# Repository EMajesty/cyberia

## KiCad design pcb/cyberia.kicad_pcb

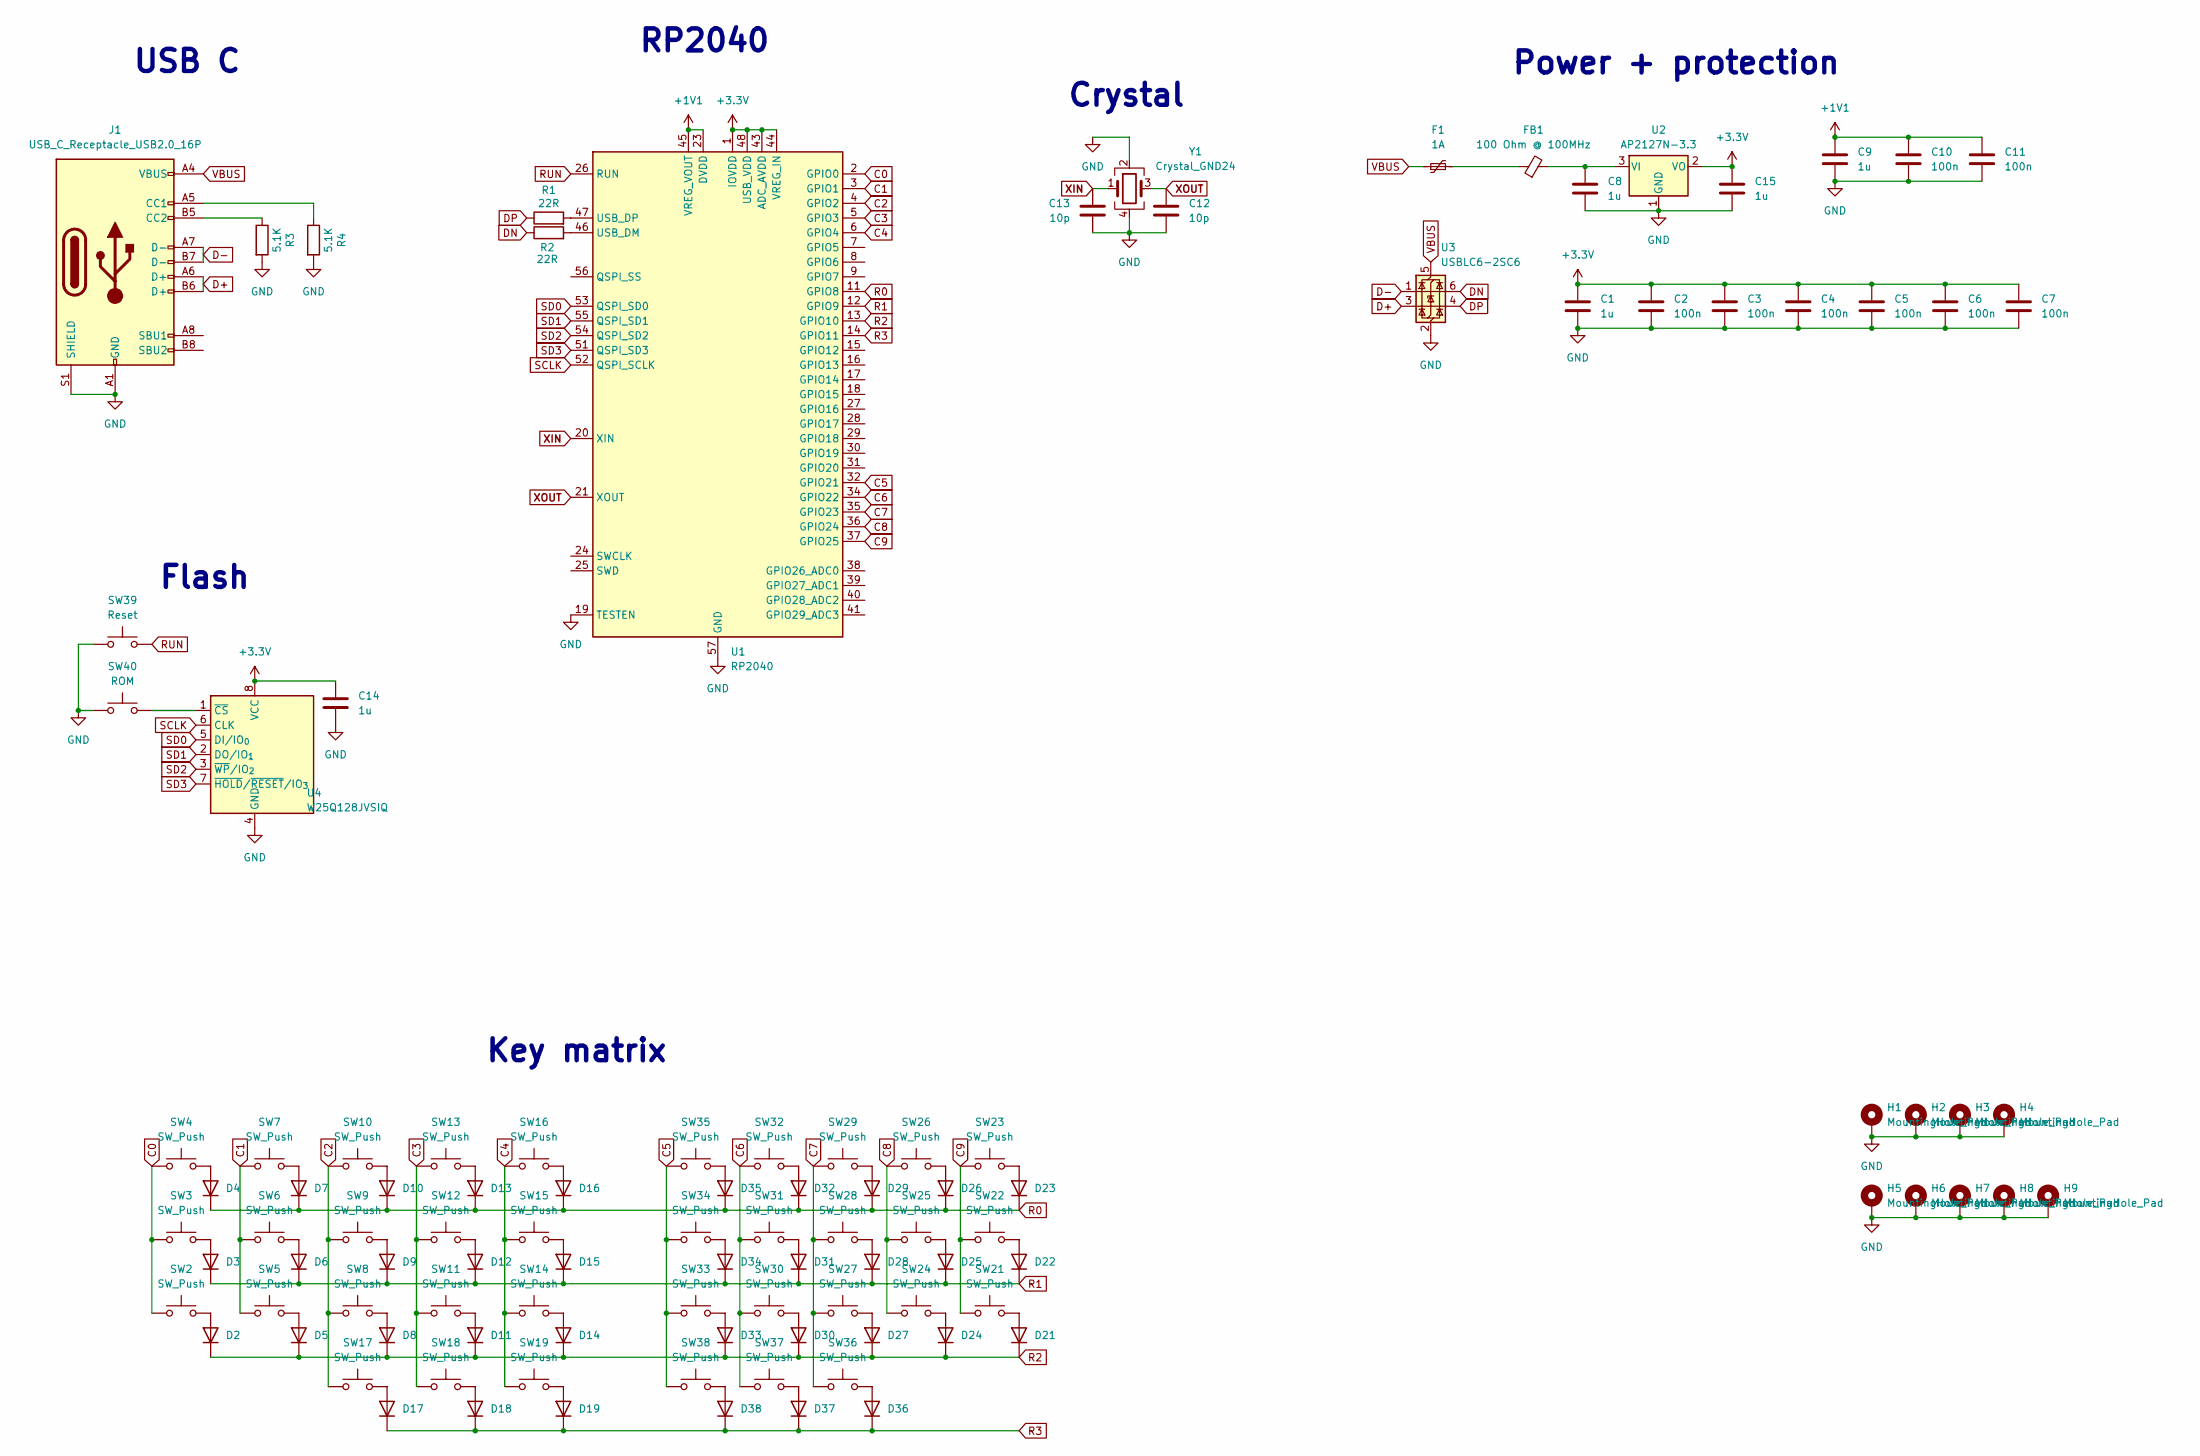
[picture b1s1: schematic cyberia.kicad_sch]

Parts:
C1, C8, C9, C14, C15: 1u; C_0603_1608Metric; LCSC C1592
C2, C3, C4, C5, C6, C7, C10, C11: 100n; C_0603_1608Metric; LCSC C1590
C12, C13: 10p; C_0603_1608Metric; LCSC C1634
D2, D3, D4, D5, D6, D7, D8, D9, D10, D11, D12, D13, D14, D15, D16, D17, D18, D19, D21, D22, D23, D24, D25, D26, D27, D28, D29, D30, D31, D32, D33, D34, D35, D36, D37, D38: D_Small_Filled; D_MiniMELF; LCSC C68883
F1: 1A; Fuse_0805_2012Metric; LCSC C20980
FB1: 100 Ohm @ 100MHz; R_0805_2012Metric; LCSC C1015
H1, H2, H3, H4, H5, H6, H7, H8, H9: MountingHole_Pad; MountingHole_3.2mm_M3
J1: USB_C_Receptacle_USB2.0_16P; USB_C_Receptacle_GCT_USB4105-xx-A_16P_TopMnt_Horizontal; LCSC C2894897
R1, R2: 22R; R_0603_1608Metric; LCSC C23345
R3, R4: 5.1K; R_0603_1608Metric; LCSC C23186
SW2, SW3, SW4, SW5, SW6, SW7, SW8, SW9, SW10, SW11, SW12, SW13, SW14, SW15, SW16, SW17, SW18, SW19, SW21, SW22, SW23, SW24, SW25, SW26, SW27, SW28, SW29, SW30, SW31, SW32, SW33, SW34, SW35, SW36, SW37, SW38: SW_Push
SW39: Reset; SW_SPST_TL3342
SW40: ROM; SW_SPST_TL3342
U1: RP2040; QFN-56-1EP_7x7mm_P0.4mm_EP3.2x3.2mm; LCSC C2040
U2: AP2127N-3.3; SOT-23; LCSC C176954
U3: USBLC6-2SC6; SOT-23-6; LCSC C7519
U4: W25Q128JVSIQ; SOIC-8_5.3x5.3mm_P1.27mm; LCSC C97521
Y1: Crystal_GND24; Crystal_SMD_3225-4Pin_3.2x2.5mm; LCSC C20625731

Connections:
+1V1: C9.1, C10.1, C11.1, U1.23 (DVDD), U1.45 (VREG_VOUT), U1.50 (DVDD)
+3.3V: C1.1, C2.1, C3.1, C4.1, C5.1, C6.1, C7.1, C14.1, C15.1, U1.1 (IOVDD), U1.10 (IOVDD), U1.22 (IOVDD), U1.33 (IOVDD), U1.42 (IOVDD), U1.43 (ADC_AVDD), U1.44 (VREG_IN), U1.48 (USB_VDD), U1.49 (IOVDD), U2.2 (VO), U4.8 (VCC)
C0: SW2.1, SW3.1, SW4.1, U1.2 (GPIO0)
C1: SW5.1, SW6.1, SW7.1, U1.3 (GPIO1)
C2: SW8.1, SW9.1, SW10.1, SW17.1, U1.4 (GPIO2)
C3: SW11.1, SW12.1, SW13.1, SW18.1, U1.5 (GPIO3)
C4: SW14.1, SW15.1, SW16.1, SW19.1, U1.6 (GPIO4)
C5: SW33.1, SW34.1, SW35.1, SW38.1, U1.32 (GPIO21)
C6: SW30.1, SW31.1, SW32.1, SW37.1, U1.34 (GPIO22)
C7: SW27.1, SW28.1, SW29.1, SW36.1, U1.35 (GPIO23)
C8: SW24.1, SW25.1, SW26.1, U1.36 (GPIO24)
C9: SW21.1, SW22.1, SW23.1, U1.37 (GPIO25)
D+: J1.A6 (D+), J1.B6 (D+), U3.3 (I/O2)
D-: J1.A7 (D-), J1.B7 (D-), U3.1 (I/O1)
DN: R2.1, U3.6 (I/O1)
DP: R1.1, U3.4 (I/O2)
GND: C1.2, C2.2, C3.2, C4.2, C5.2, C6.2, C7.2, C8.2, C9.2, C10.2, C11.2, C12.2, C13.2, C14.2, C15.2, H1.1, H2.1, H3.1, H4.1, H5.1, H6.1, H7.1, H8.1, H9.1, J1.A1 (GND), J1.A12 (GND), J1.B1 (GND), J1.B12 (GND), J1.S1 (SHIELD), R3.2, R4.2, SW39.1, SW40.1, U1.19 (TESTEN), U1.57 (GND), U2.1 (GND), U3.2 (GND), U4.4 (GND), Y1.2, Y1.4
unnamed: D2.2 (A), SW2.2
unnamed: D3.2 (A), SW3.2
unnamed: D4.2 (A), SW4.2
unnamed: D5.2 (A), SW5.2
unnamed: D6.2 (A), SW6.2
unnamed: D7.2 (A), SW7.2
unnamed: D8.2 (A), SW8.2
unnamed: D9.2 (A), SW9.2
unnamed: D10.2 (A), SW10.2
unnamed: D11.2 (A), SW11.2
unnamed: D12.2 (A), SW12.2
unnamed: D13.2 (A), SW13.2
unnamed: D14.2 (A), SW14.2
unnamed: D15.2 (A), SW15.2
unnamed: D16.2 (A), SW16.2
unnamed: D17.2 (A), SW17.2
unnamed: D18.2 (A), SW18.2
unnamed: D19.2 (A), SW19.2
unnamed: D21.2 (A), SW21.2
unnamed: D22.2 (A), SW22.2
unnamed: D23.2 (A), SW23.2
unnamed: D24.2 (A), SW24.2
unnamed: D25.2 (A), SW25.2
unnamed: D26.2 (A), SW26.2
unnamed: D27.2 (A), SW27.2
unnamed: D28.2 (A), SW28.2
unnamed: D29.2 (A), SW29.2
unnamed: D30.2 (A), SW30.2
unnamed: D31.2 (A), SW31.2
unnamed: D32.2 (A), SW32.2
unnamed: D33.2 (A), SW33.2
unnamed: D34.2 (A), SW34.2
unnamed: D35.2 (A), SW35.2
unnamed: D36.2 (A), SW36.2
unnamed: D37.2 (A), SW37.2
unnamed: D38.2 (A), SW38.2
unnamed: F1.2, FB1.1
unnamed: J1.A5 (CC1), R4.1
unnamed: J1.B5 (CC2), R3.1
unnamed: R2.2, U1.46 (USB_DM)
unnamed: R1.2, U1.47 (USB_DP)
unnamed: C8.1, FB1.2, U2.3 (VI)
unnamed: SW40.2, U4.1 (~CS)
R0: D4.1 (K), D7.1 (K), D10.1 (K), D13.1 (K), D16.1 (K), D23.1 (K), D26.1 (K), D29.1 (K), D32.1 (K), D35.1 (K), U1.11 (GPIO8)
R1: D3.1 (K), D6.1 (K), D9.1 (K), D12.1 (K), D15.1 (K), D22.1 (K), D25.1 (K), D28.1 (K), D31.1 (K), D34.1 (K), U1.12 (GPIO9)
R2: D2.1 (K), D5.1 (K), D8.1 (K), D11.1 (K), D14.1 (K), D21.1 (K), D24.1 (K), D27.1 (K), D30.1 (K), D33.1 (K), U1.13 (GPIO10)
R3: D17.1 (K), D18.1 (K), D19.1 (K), D36.1 (K), D37.1 (K), D38.1 (K), U1.14 (GPIO11)
RUN: SW39.2, U1.26 (RUN)
SCLK: U1.52 (QSPI_SCLK), U4.6 (CLK)
SD0: U1.53 (QSPI_SD0), U4.5 (DI/IO_{0})
SD1: U1.55 (QSPI_SD1), U4.2 (DO/IO_{1})
SD2: U1.54 (QSPI_SD2), U4.3 (~WP/IO_{2})
SD3: U1.51 (QSPI_SD3), U4.7 (~HOLD/~RESET/IO_{3})
VBUS: F1.1, J1.A4 (VBUS), J1.A9 (VBUS), J1.B4 (VBUS), J1.B9 (VBUS), U3.5 (VBUS)
XIN: C13.1, U1.20 (XIN), Y1.1
XOUT: C12.1, U1.21 (XOUT), Y1.3

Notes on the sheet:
Key matrix
Power + protection
RP2040
USB C
Flash
Crystal

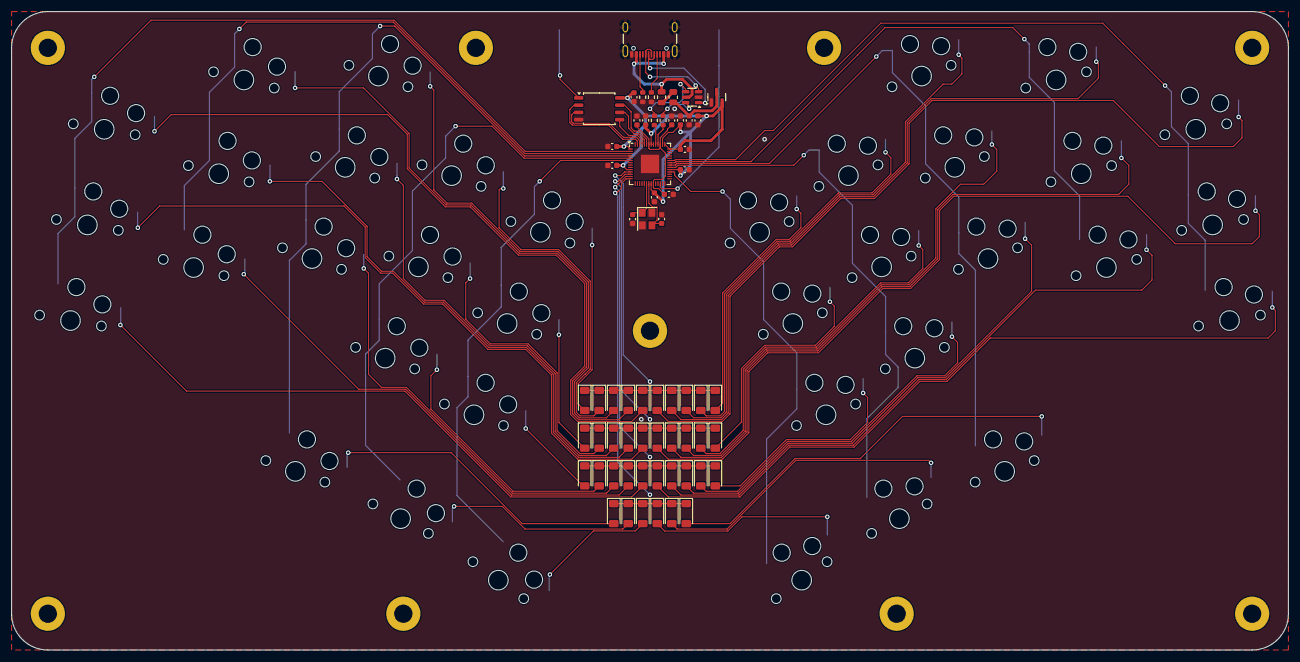
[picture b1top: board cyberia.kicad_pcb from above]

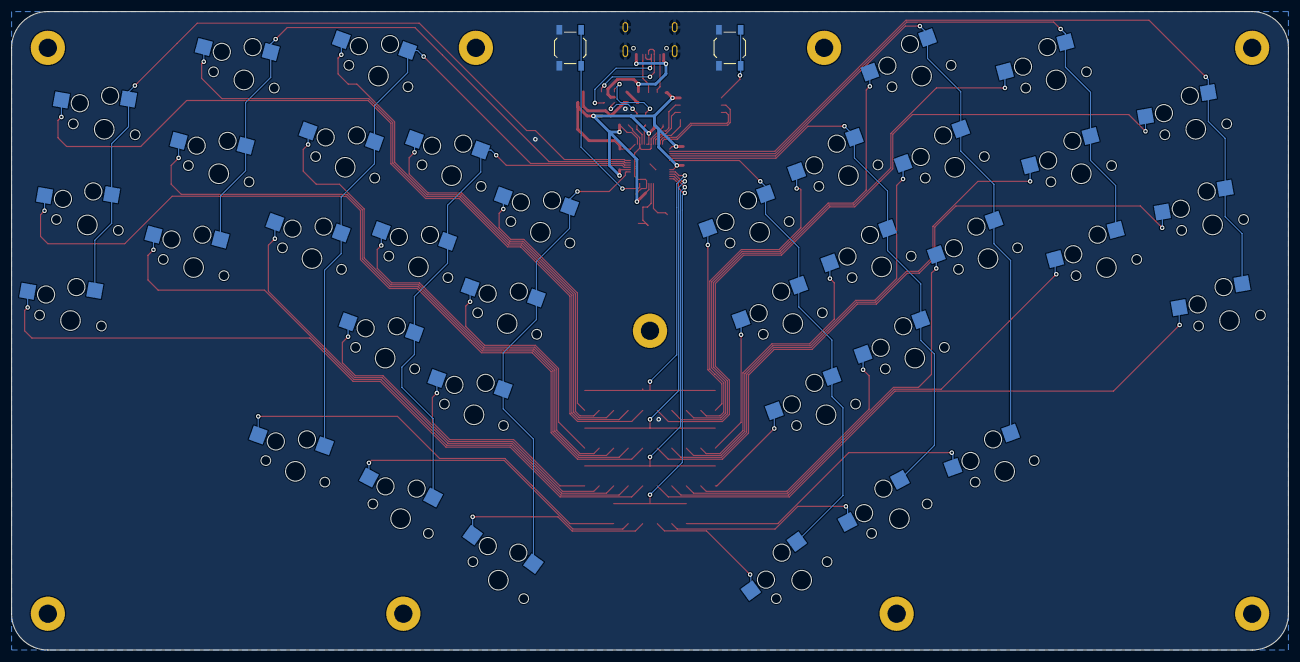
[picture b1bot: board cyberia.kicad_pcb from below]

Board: 2 copper layers, 223.5 x 111.8 mm, 110 parts (2 on the bottom side), 73 nets.

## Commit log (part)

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2025-07-07 init
2025-07-07 readme
2025-07-07 fix some drc errors
2025-07-07 bigger pic
2025-07-16 rev.666
2025-07-28 v0.666
2025-07-28 cleanup
2025-07-28 update photo
2025-09-22 dunno
